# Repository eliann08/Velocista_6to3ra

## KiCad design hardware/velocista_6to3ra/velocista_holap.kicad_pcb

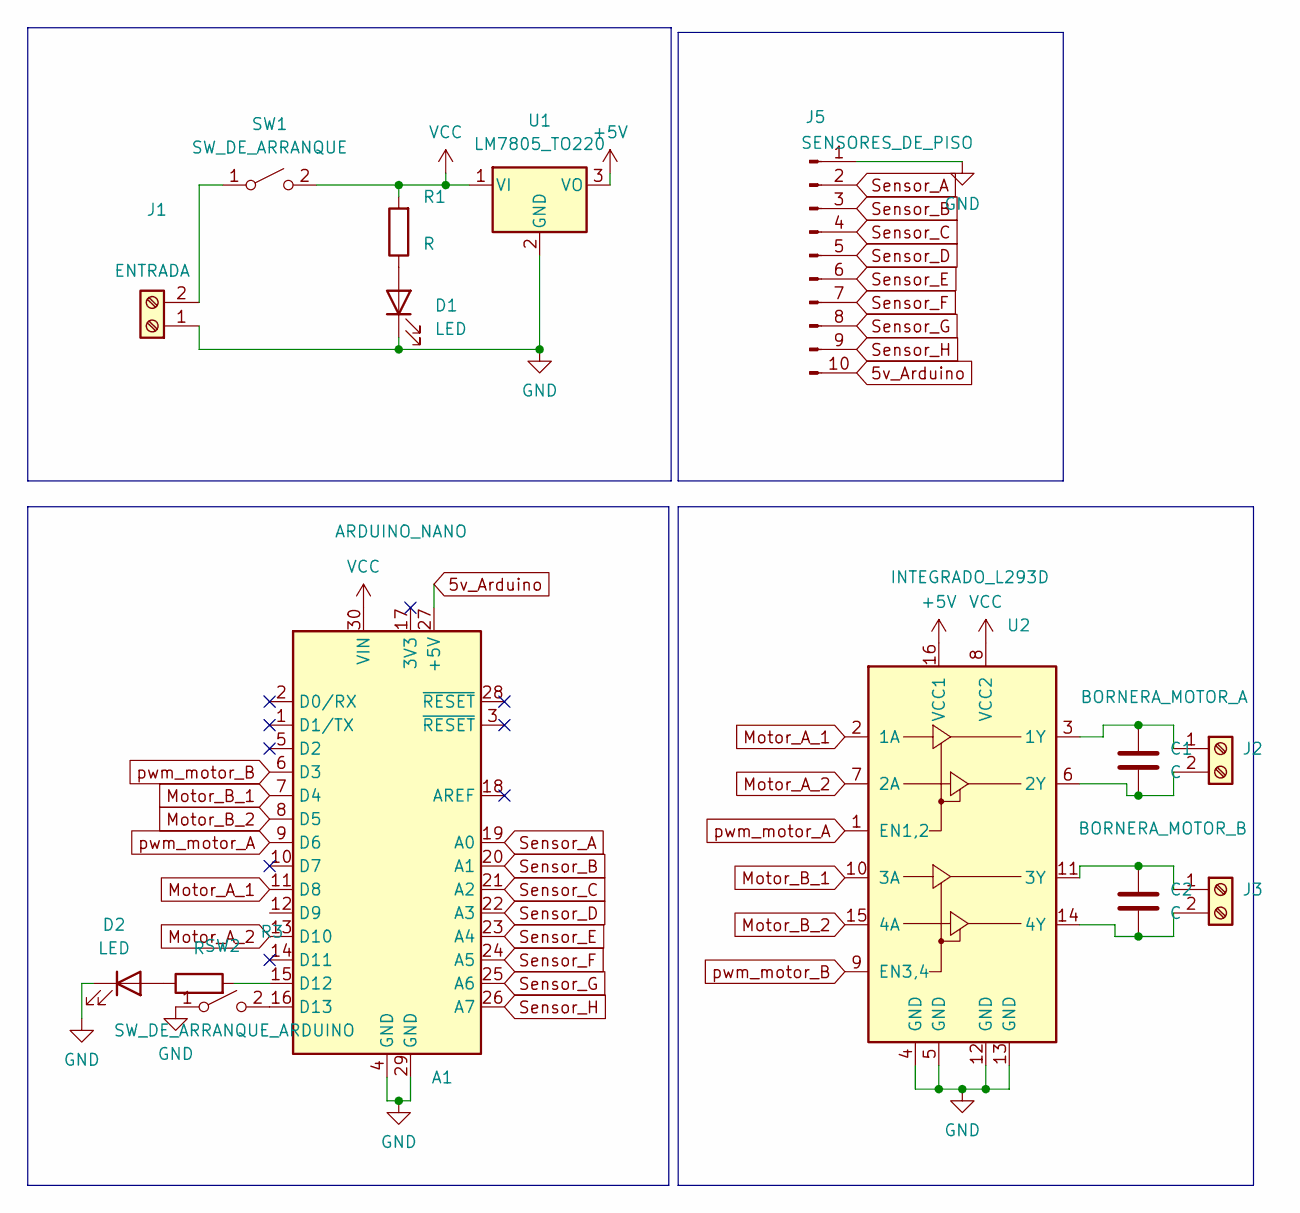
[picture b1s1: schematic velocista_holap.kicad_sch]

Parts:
A1: ARDUINO_NANO; Arduino_Nano
C1, C2: C; C_Disc_D4.7mm_W2.5mm_P5.00mm
D1, D2: LED; LED_D5.0mm_IRGrey
J1: ENTRADA; TerminalBlock_Altech_AK300-2_P5.00mm
J2: BORNERA_MOTOR_A; TerminalBlock_Altech_AK300-2_P5.00mm
J3: BORNERA_MOTOR_B; TerminalBlock_Altech_AK300-2_P5.00mm
J5: SENSORES_DE_PISO; PinHeader_1x10_P2.54mm_Vertical
R1, R3: R; R_Axial_DIN0207_L6.3mm_D2.5mm_P10.16mm_Horizontal
SW1: SW_DE_ARRANQUE; SW_100SP1T1B4M2QE
SW2: SW_DE_ARRANQUE_ARDUINO; SW_Tactile_Straight_KSA0Axx1LFTR
U1: LM7805_TO220; TO-220-2
U2: INTEGRADO_L293D; DIP-16_W7.62mm

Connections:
5v_Arduino: A1.27 (+5V), J5.10
+5V: U1.3 (VO), U2.16 (VCC1)
GND: A1.4 (GND), A1.29 (GND), D1.1 (K), D2.1 (K), J1.1, J5.1, SW2.1 (A), U1.2 (GND), U2.4 (GND), U2.5 (GND), U2.12 (GND), U2.13 (GND)
Motor_A_1: A1.11 (D8), U2.2 (1A)
Motor_A_2: A1.13 (D10), U2.7 (2A)
Motor_B_1: A1.7 (D4), U2.10 (3A)
Motor_B_2: A1.8 (D5), U2.15 (4A)
unnamed: A1.15 (D12), R3.2
unnamed: A1.16 (D13), SW2.2 (B)
unnamed: D1.2 (A), R1.1
unnamed: D2.2 (A), R3.1
unnamed: J1.2, SW1.1 (A)
unnamed: C1.1, J2.1, U2.3 (1Y)
unnamed: C1.2, J2.2, U2.6 (2Y)
unnamed: C2.1, J3.1, U2.11 (3Y)
unnamed: C2.2, J3.2, U2.14 (4Y)
Sensor_A: A1.19 (A0), J5.2
Sensor_B: A1.20 (A1), J5.3
Sensor_C: A1.21 (A2), J5.4
Sensor_D: A1.22 (A3), J5.5
Sensor_E: A1.23 (A4), J5.6
Sensor_F: A1.24 (A5), J5.7
Sensor_G: A1.25 (A6), J5.8
Sensor_H: A1.26 (A7), J5.9
VCC: A1.30 (VIN), R1.2, SW1.2 (B), U1.1 (VI), U2.8 (VCC2)
pwm_motor_A: A1.9 (D6), U2.1 (EN1,2)
pwm_motor_B: A1.6 (D3), U2.9 (EN3,4)

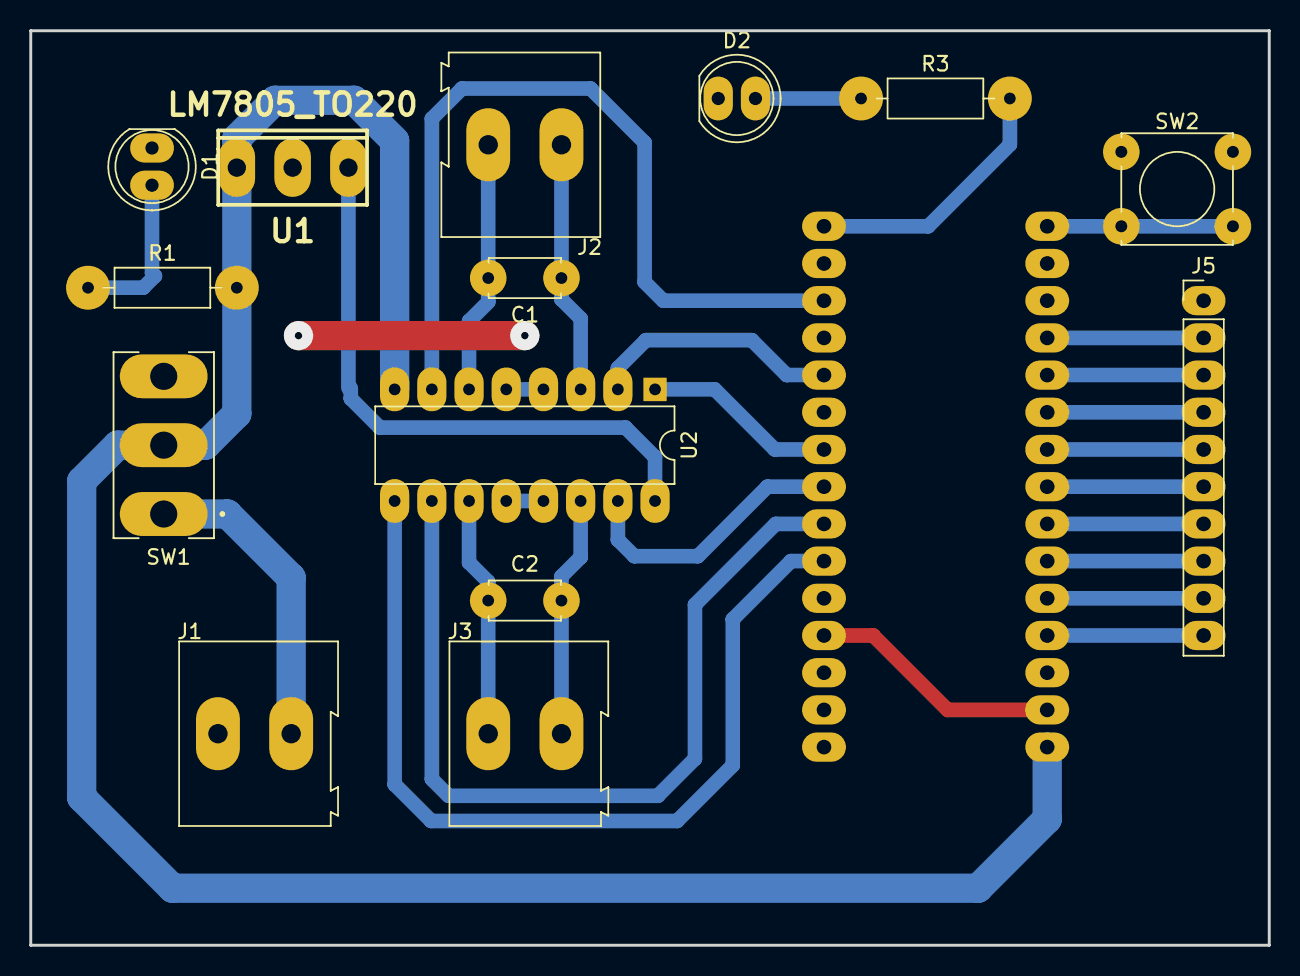
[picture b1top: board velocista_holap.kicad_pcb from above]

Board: 2 copper layers, 84.6 x 62.4 mm, 15 parts (1 on the bottom side), 27 nets.

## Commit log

2025-10-27 Velocista_27_octubre
2025-10-29 29/10
2025-10-29 29/10_2
